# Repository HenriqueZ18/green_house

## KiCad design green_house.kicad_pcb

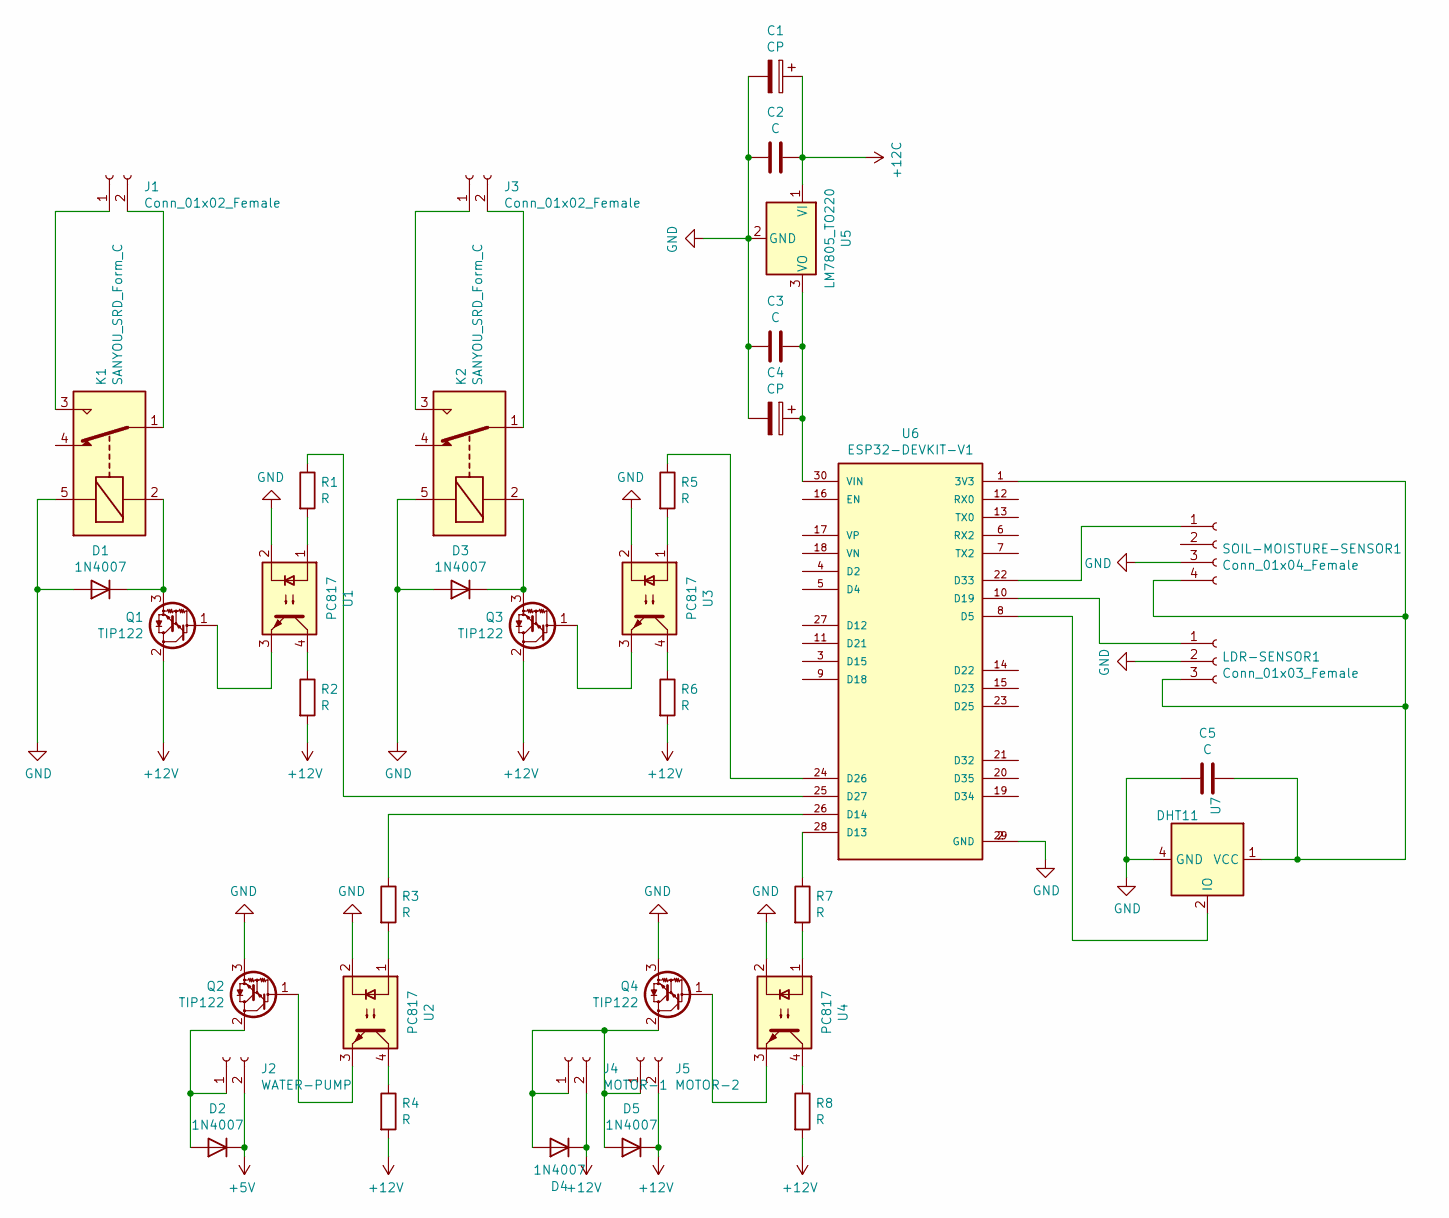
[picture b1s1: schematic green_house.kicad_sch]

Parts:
C1, C4: CP; C_Radial_D12.5mm_H25.0mm_P5.00mm
C2, C3, C5: C; C_Radial_D12.5mm_H25.0mm_P5.00mm
D1, D2, D3, D4, D5: 1N4007; D_DO-41_SOD81_P10.16mm_Horizontal
J1, J3: Conn_01x02_Female; TestPoint_2Pads_Pitch5.08mm_Drill1.3mm
J2: WATER-PUMP; TestPoint_2Pads_Pitch5.08mm_Drill1.3mm
J4: MOTOR-1; TestPoint_2Pads_Pitch5.08mm_Drill1.3mm
J5: MOTOR-2; TestPoint_2Pads_Pitch5.08mm_Drill1.3mm
K1, K2: SANYOU_SRD_Form_C; Relay_SPDT_SANYOU_SRD_Series_Form_C
LDR-SENSOR1: Conn_01x03_Female; TerminalBlock_4Ucon_1x03_P3.50mm_Vertical
Q1, Q2, Q3, Q4: TIP122; TO-220-3_Vertical
R1, R2, R3, R4, R5, R6, R7, R8: R; R_Axial_DIN0614_L14.3mm_D5.7mm_P25.40mm_Horizontal
SOIL-MOISTURE-SENSOR1: Conn_01x04_Female; TerminalBlock_4Ucon_1x04_P3.50mm_Horizontal
U1, U2, U3, U4: PC817; DIP-4_W7.62mm
U5: LM7805_TO220; TO-220-3_Vertical
U6: ESP32-DEVKIT-V1; MODULE_ESP32_DEVKIT_V1; PARTREV N/A
U7: DHT11; Aosong_DHT11_5.5x12.0_P2.54mm

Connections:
+5V: D2.1 (K), J2.2
+12C: C1.1, C2.1, U5.1 (VI)
GND: C1.2, C2.2, C3.2, C4.2, C5.2, D1.2 (A), D3.2 (A), K1.5, K2.5, LDR-SENSOR1.2, Q2.3 (E), Q4.3 (E), SOIL-MOISTURE-SENSOR1.3, U1.2, U2.2, U3.2, U4.2, U5.2 (GND), U6.2 (GND), U6.29 (GND), U7.4 (GND)
unnamed: C3.1, C4.1, U5.3 (VO), U6.30 (VIN)
unnamed: D1.1 (K), K1.2, Q1.3 (E)
unnamed: D2.2 (A), J2.1, Q2.2 (C)
unnamed: D3.1 (K), K2.2, Q3.3 (E)
unnamed: J1.1, K1.3
unnamed: J1.2, K1.1
unnamed: J3.1, K2.3
unnamed: J3.2, K2.1
unnamed: LDR-SENSOR1.1, U6.10 (D19)
unnamed: C5.1, LDR-SENSOR1.3, SOIL-MOISTURE-SENSOR1.4, U6.1 (3V3), U7.1 (VCC)
unnamed: Q1.1 (B), U1.3
unnamed: Q2.1 (B), U2.3
unnamed: Q3.1 (B), U3.3
unnamed: Q4.1 (B), U4.3
unnamed: R1.1, U6.25 (D27)
unnamed: R1.2, U1.1
unnamed: R2.1, U1.4
unnamed: R3.1, U6.26 (D14)
unnamed: R3.2, U2.1
unnamed: R4.1, U2.4
unnamed: R5.1, U6.24 (D26)
unnamed: R5.2, U3.1
unnamed: R6.1, U3.4
unnamed: R7.1, U6.28 (D13)
unnamed: R7.2, U4.1
unnamed: R8.1, U4.4
unnamed: SOIL-MOISTURE-SENSOR1.1, U6.22 (D33)
unnamed: U6.8 (D5), U7.2 (IO)

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
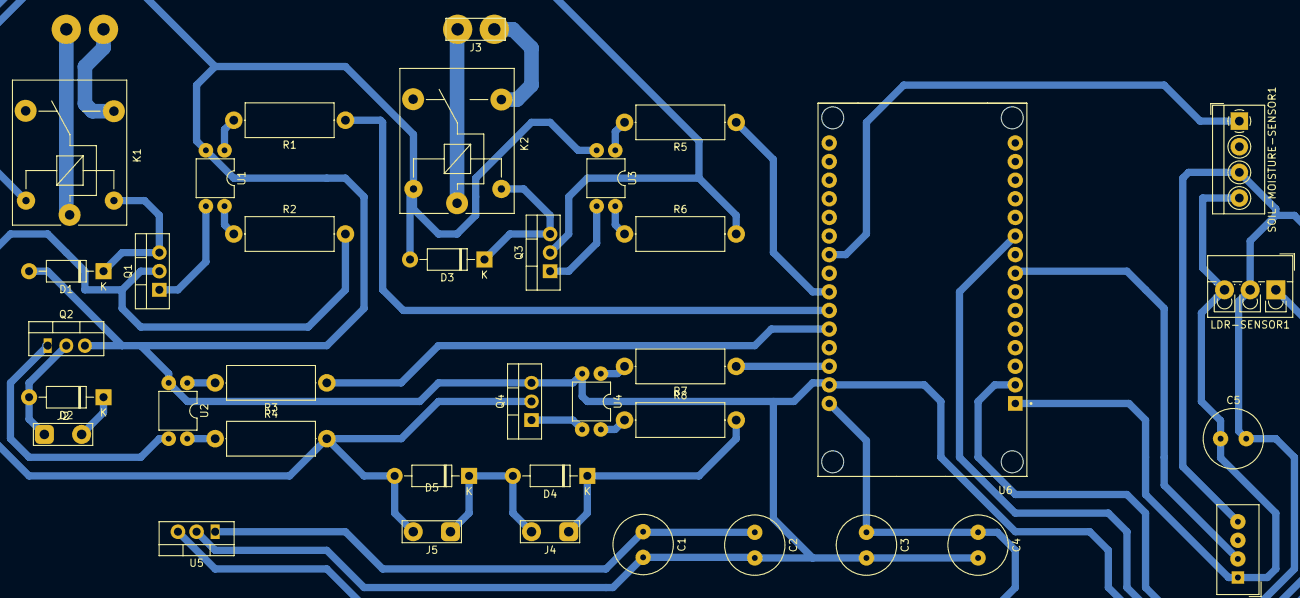
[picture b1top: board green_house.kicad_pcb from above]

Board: 2 copper layers, 37 parts (0 on the bottom side), 30 nets.

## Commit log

2023-10-10 removed backups
2023-10-10 changed relay track size to 2mm
2023-11-11 fixed pads and holes dimensions
